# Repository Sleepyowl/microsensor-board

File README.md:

# Microsensor Board

This is a complete KiCad project of a miniature multiprotocol temperature and humidity sensor based on nRF54 SoC and HDC2080 sensor.

An example firmware for the board can be found here: [microsensor-firmware](https://github.com/Sleepyowl/microsensor-firmware).

# Features

- 4 layer PCB layout
    - NB: earlier versions routed with 2 layers
- External RTC allows System Off sleep enabling ultra-low power consumption
- SoC supports BLE, ZigBee and Thread
- Miniature 6-pin Tag-Connect for firmware burning and debugging
- Button and LED
- Backside pads for CR20xx

# Issues

- No reverse polarity or overvoltage protection (I don't need it for my application)

# Manufacturing

I have manufactured working prototypes on PCBWay with the following parameters:

| Parameter              | Value            |
|------------------------|------------------|
| Layers                 | 4                |
| Thickness              | 1.6 mm           |
| Min Track / Spacing    | 4 / 4 mil        |
| Min Hole Size          | 0.3 mm           |
| Surface Finish         | ENIG             |

While it is possile get working boards with HASL lead-free, it might require manual retouching of some parts (e.g. RTC chip).

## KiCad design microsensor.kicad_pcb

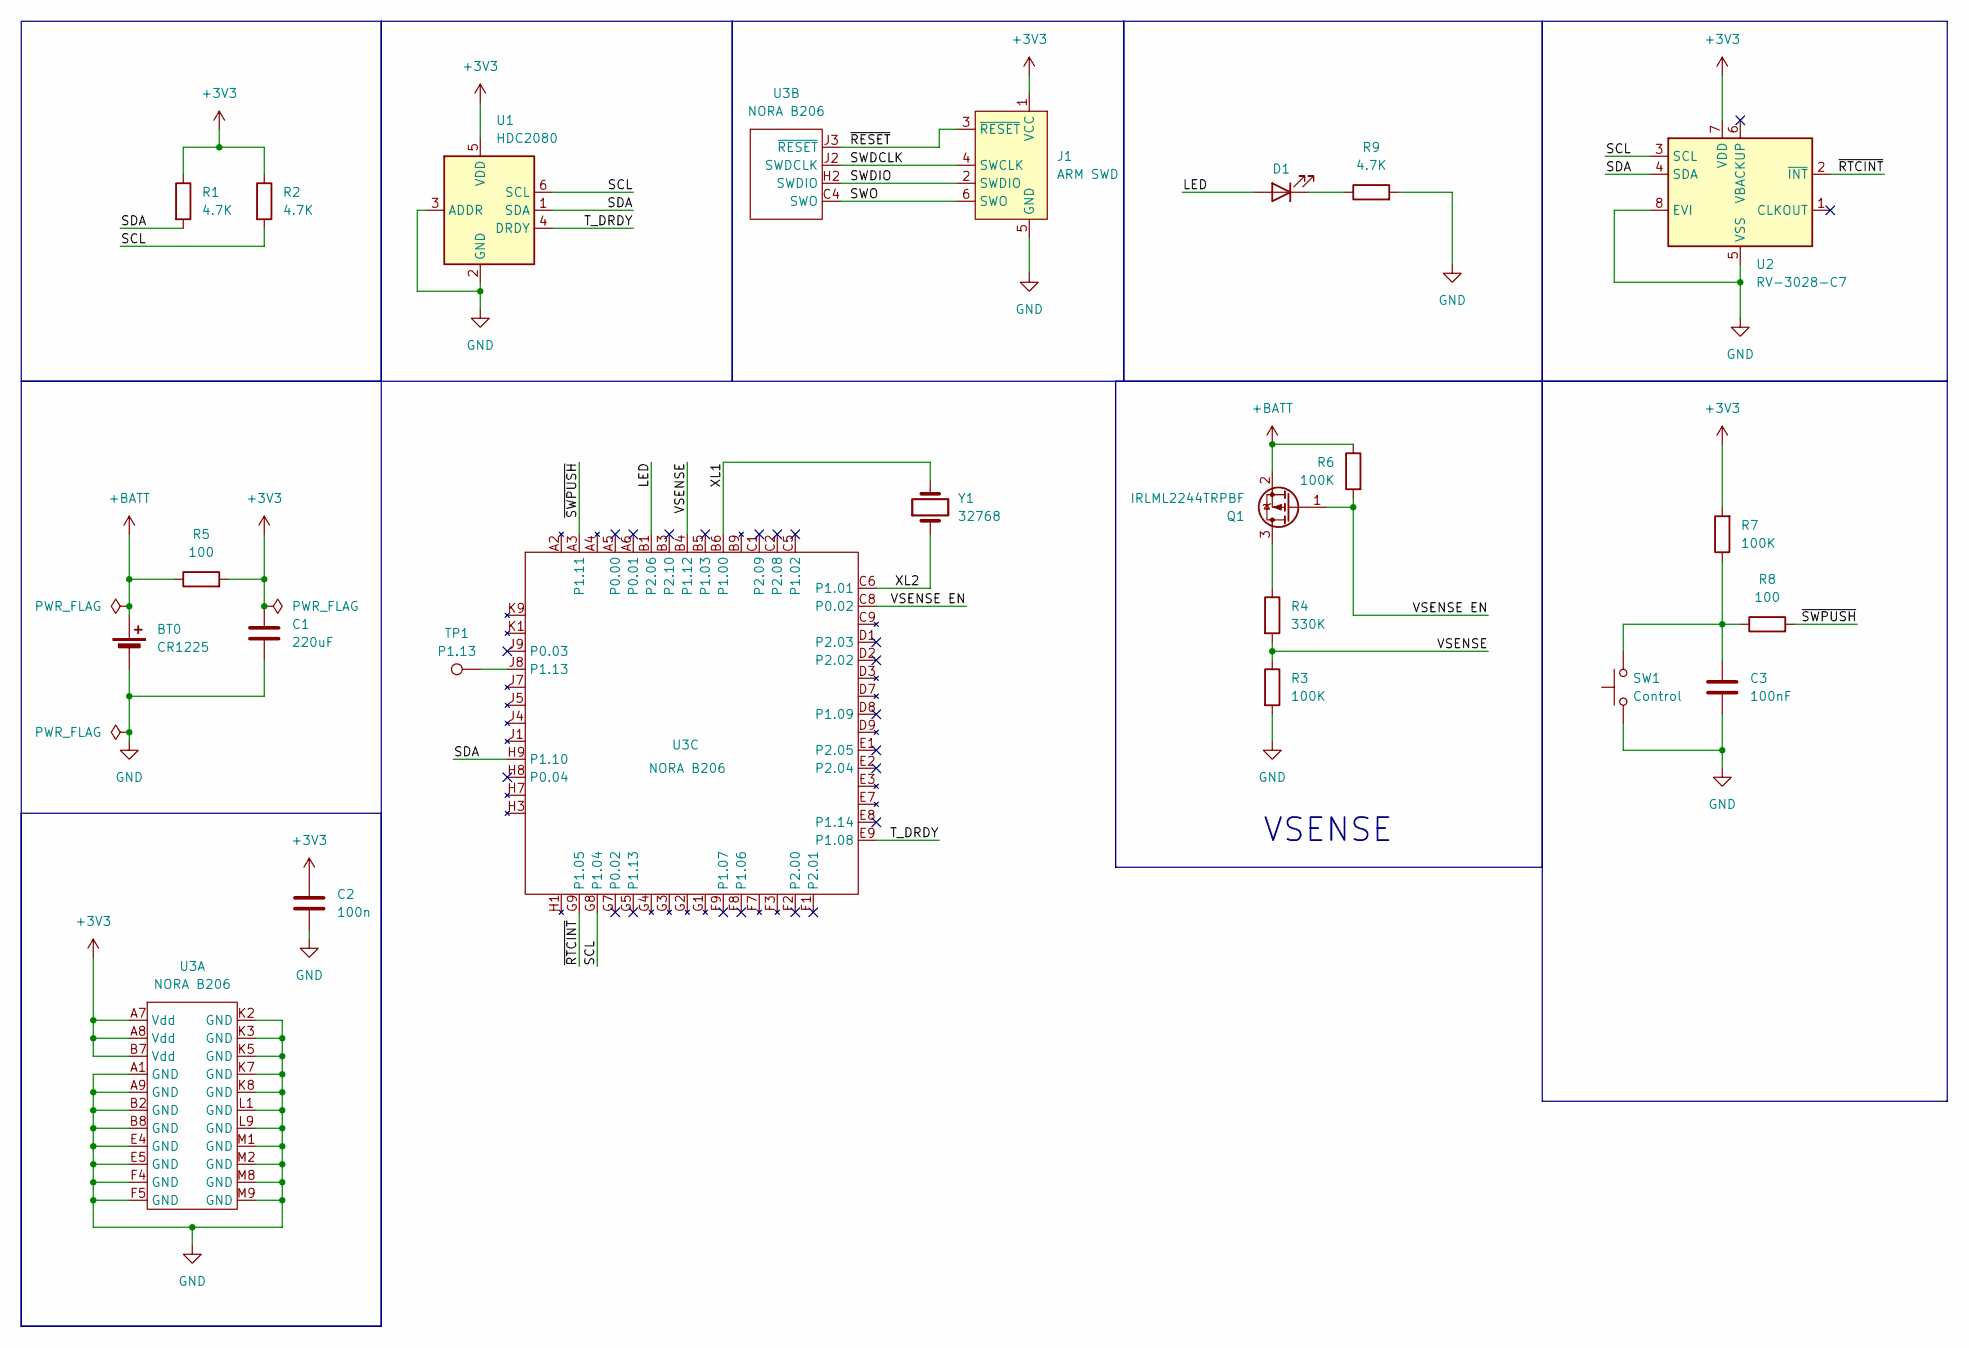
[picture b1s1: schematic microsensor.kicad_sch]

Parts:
BT0: CR1225; Keystone 110 and 112 for CR20xx
C1: 220uF; C_1206_3216Metric
C2: 100n; C_0805_2012Metric
C3: 100nF; C_0805_2012Metric
D1: LED; LED_1206_3216Metric
J1: ARM SWD; Tag-Connect_TC2030-IDC-NL_2x03_P1.27mm_Vertical
Q1: IRLML2244TRPBF; SOT-23
R1, R2, R9: 4.7K; R_0805_2012Metric
R3, R6, R7: 100K; R_0805_2012Metric
R4: 330K; R_0805_2012Metric
R5, R8: 100; R_0805_2012Metric
SW1: Control; B3U-1000P
TP1: P1.13; TestPoint_Pad_1.5x1.5mm
U1: HDC2080; Texas_S-PWSON-N6-HDC2080
U2: RV-3028-C7; MicroCrystal_C7_SON-8_1.5x3.2mm_P0.9mm
U3: NORA B206; NORA-B2x6
Y1: 32768; Crystal_SMD_2012-2Pin_2.0x1.2mm

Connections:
+3V3: C1.1, C2.1, J1.1 (VCC), R1.1, R2.1, R5.2, R7.2, U1.5 (VDD), U2.7 (VDD), U3.A7 (Vdd), U3.A8 (Vdd), U3.B7 (Vdd)
+BATT: BT0.1 (+), Q1.2 (S), R5.1, R6.1
/LED: D1.2 (A), U3.B1 (P2.06)
/SCL: R2.2, U1.6 (SCL), U2.3 (SCL), U3.G8 (P1.04)
/SDA: R1.2, U1.1 (SDA), U2.4 (SDA), U3.H9 (P1.10)
/SWDCLK: J1.4 (SWCLK), U3.J2 (SWDCLK)
/SWDIO: J1.2 (SWDIO), U3.H2 (SWDIO)
/SWO: J1.6 (SWO), U3.C4 (SWO)
/T_DRDY: U1.4 (DRDY), U3.E9 (P1.08)
/VSENSE: R3.1, R4.2, U3.B4 (P1.12)
/VSENSE EN: Q1.1 (G), R6.2, U3.C8 (P0.02)
/XL1: U3.B6 (P1.00), Y1.2
/XL2: U3.C6 (P1.01), Y1.1
/~RESET: J1.3 (~RESET), U3.J3 (~RESET)
/~RTCINT: U2.2 (~INT), U3.G9 (P1.05)
/~SWPUSH: R8.2, U3.A3 (P1.11)
GND: BT0.2 (-), C1.2, C2.2, C3.2, J1.5 (GND), R3.2, R9.2, SW1.1, U1.2 (GND), U1.3 (ADDR), U2.5 (VSS), U2.8 (EVI), U3.A1 (GND), U3.A9 (GND), U3.B2 (GND), U3.B8 (GND), U3.E4 (GND), U3.E5 (GND), U3.F4 (GND), U3.F5 (GND), U3.K2 (GND), U3.K3 (GND), U3.K5 (GND), U3.K7 (GND), U3.K8 (GND), U3.L1 (GND), U3.L9 (GND), U3.M1 (GND), U3.M2 (GND), U3.M8 (GND), U3.M9 (GND)
unnamed: C3.1, R7.1, R8.1, SW1.2
unnamed: D1.1 (K), R9.1
unnamed: Q1.3 (D), R4.1
unnamed: TP1.1 (1_1), U3.J8 (P1.13)

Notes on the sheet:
VSENSE

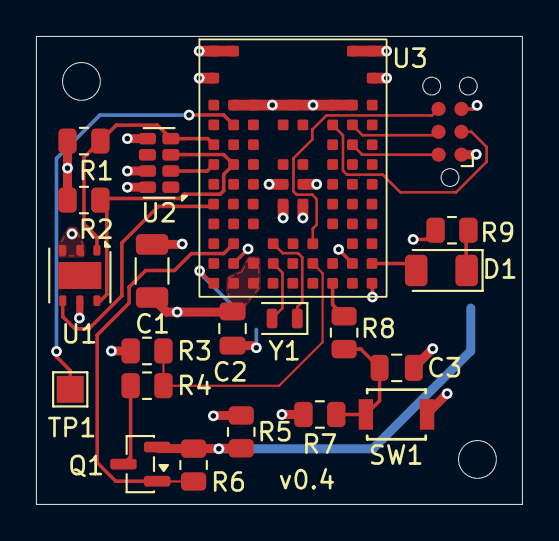
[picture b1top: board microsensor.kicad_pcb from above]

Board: 4 copper layers, 27.0 x 26.0 mm, 24 parts (1 on the bottom side), 21 nets.

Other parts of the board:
MH1, MH2: MountingHole_2.1mm

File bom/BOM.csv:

"Reference","Value","Datasheet","Footprint","Qty","DNP"
"BT0","CR1225","","footprints:Keystone 110 and 112 for CR20xx","1",""
"C1","220uF","","Capacitor_SMD:C_1206_3216Metric","1",""
"C2,C3","0.1u","","Capacitor_SMD:C_0805_2012Metric","2",""
"D1","LED","","LED_SMD:LED_1206_3216Metric","1",""
"Q1","IRLML2244TRPBF","https://www.infineon.com/dgdl/irlml2244pbf.pdf?fileId=5546d4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","Package_TO_SOT_SMD:SOT-23","1",""
"R1,R2,R9","4.7K","","Resistor_SMD:R_0805_2012Metric","3",""
"R3,R6,R7","100K","","Resistor_SMD:R_0805_2012Metric","3",""
"R4","330K","","Resistor_SMD:R_0805_2012Metric","1",""
"R5,R8","100","","Resistor_SMD:R_0805_2012Metric","2",""
"SW1","Control","","footprints:B3U-1000P","1",""
"U1","HDC2080","http://www.ti.com/lit/ds/symlink/hdc2080.pdf","Sensor_Humidity:Texas_S-PWSON-N6-HDC2080","1",""
"U2","RV-3028-C7","https://www.microcrystal.com/fileadmin/Media/Products/RTC/Da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","Package_SON:MicroCrystal_C7_SON-8_1.5x3.2mm_P0.9mm","1",""
"U3","NORA B206","","footprints:NORA-B2x6","1",""
"Y1","32768","","Crystal:Crystal_SMD_2012-2Pin_2.0x1.2mm","1",""

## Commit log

2025-10-23 Shrink to 45x35 Unify R sizes to 0805 Rearrange Add dimensions (User layer)
2025-10-23 Ver 0.1 finalized and ordered
2025-10-23 Added bom related properties
2025-10-31 Add gerbers submitted for v0.1
2025-11-03 Smaller version 25mmx25mm
2025-11-06 Change battery holder, update layout
2025-11-08 Switch to nRF54L15 (NORA B206)
2025-11-25 Finalize routing for NORA module Add and route VSENSE circuit
2025-12-04 v0.2 gerbers
2025-12-05 v0.2 BOM + document with issues
2025-12-09 Fix I2C routed to invalid pins Remove unnecessary N-MOS Adjust placement and routing Adjust annotations (order topologically)
2025-12-09 Adjust board constraints Add CAM files for version 0.3
2026-04-14 v0.4 Switched to 4 layers Minor re-routing Changed button to smaller model Added mounting holes Added some missing 3d models
2026-04-16 Add CAM for v0.4 (as ordered)
2026-04-16 Update BOM, add DigiKey list with parts
2026-04-16 Update thickness in README (was the value for 2L board)
